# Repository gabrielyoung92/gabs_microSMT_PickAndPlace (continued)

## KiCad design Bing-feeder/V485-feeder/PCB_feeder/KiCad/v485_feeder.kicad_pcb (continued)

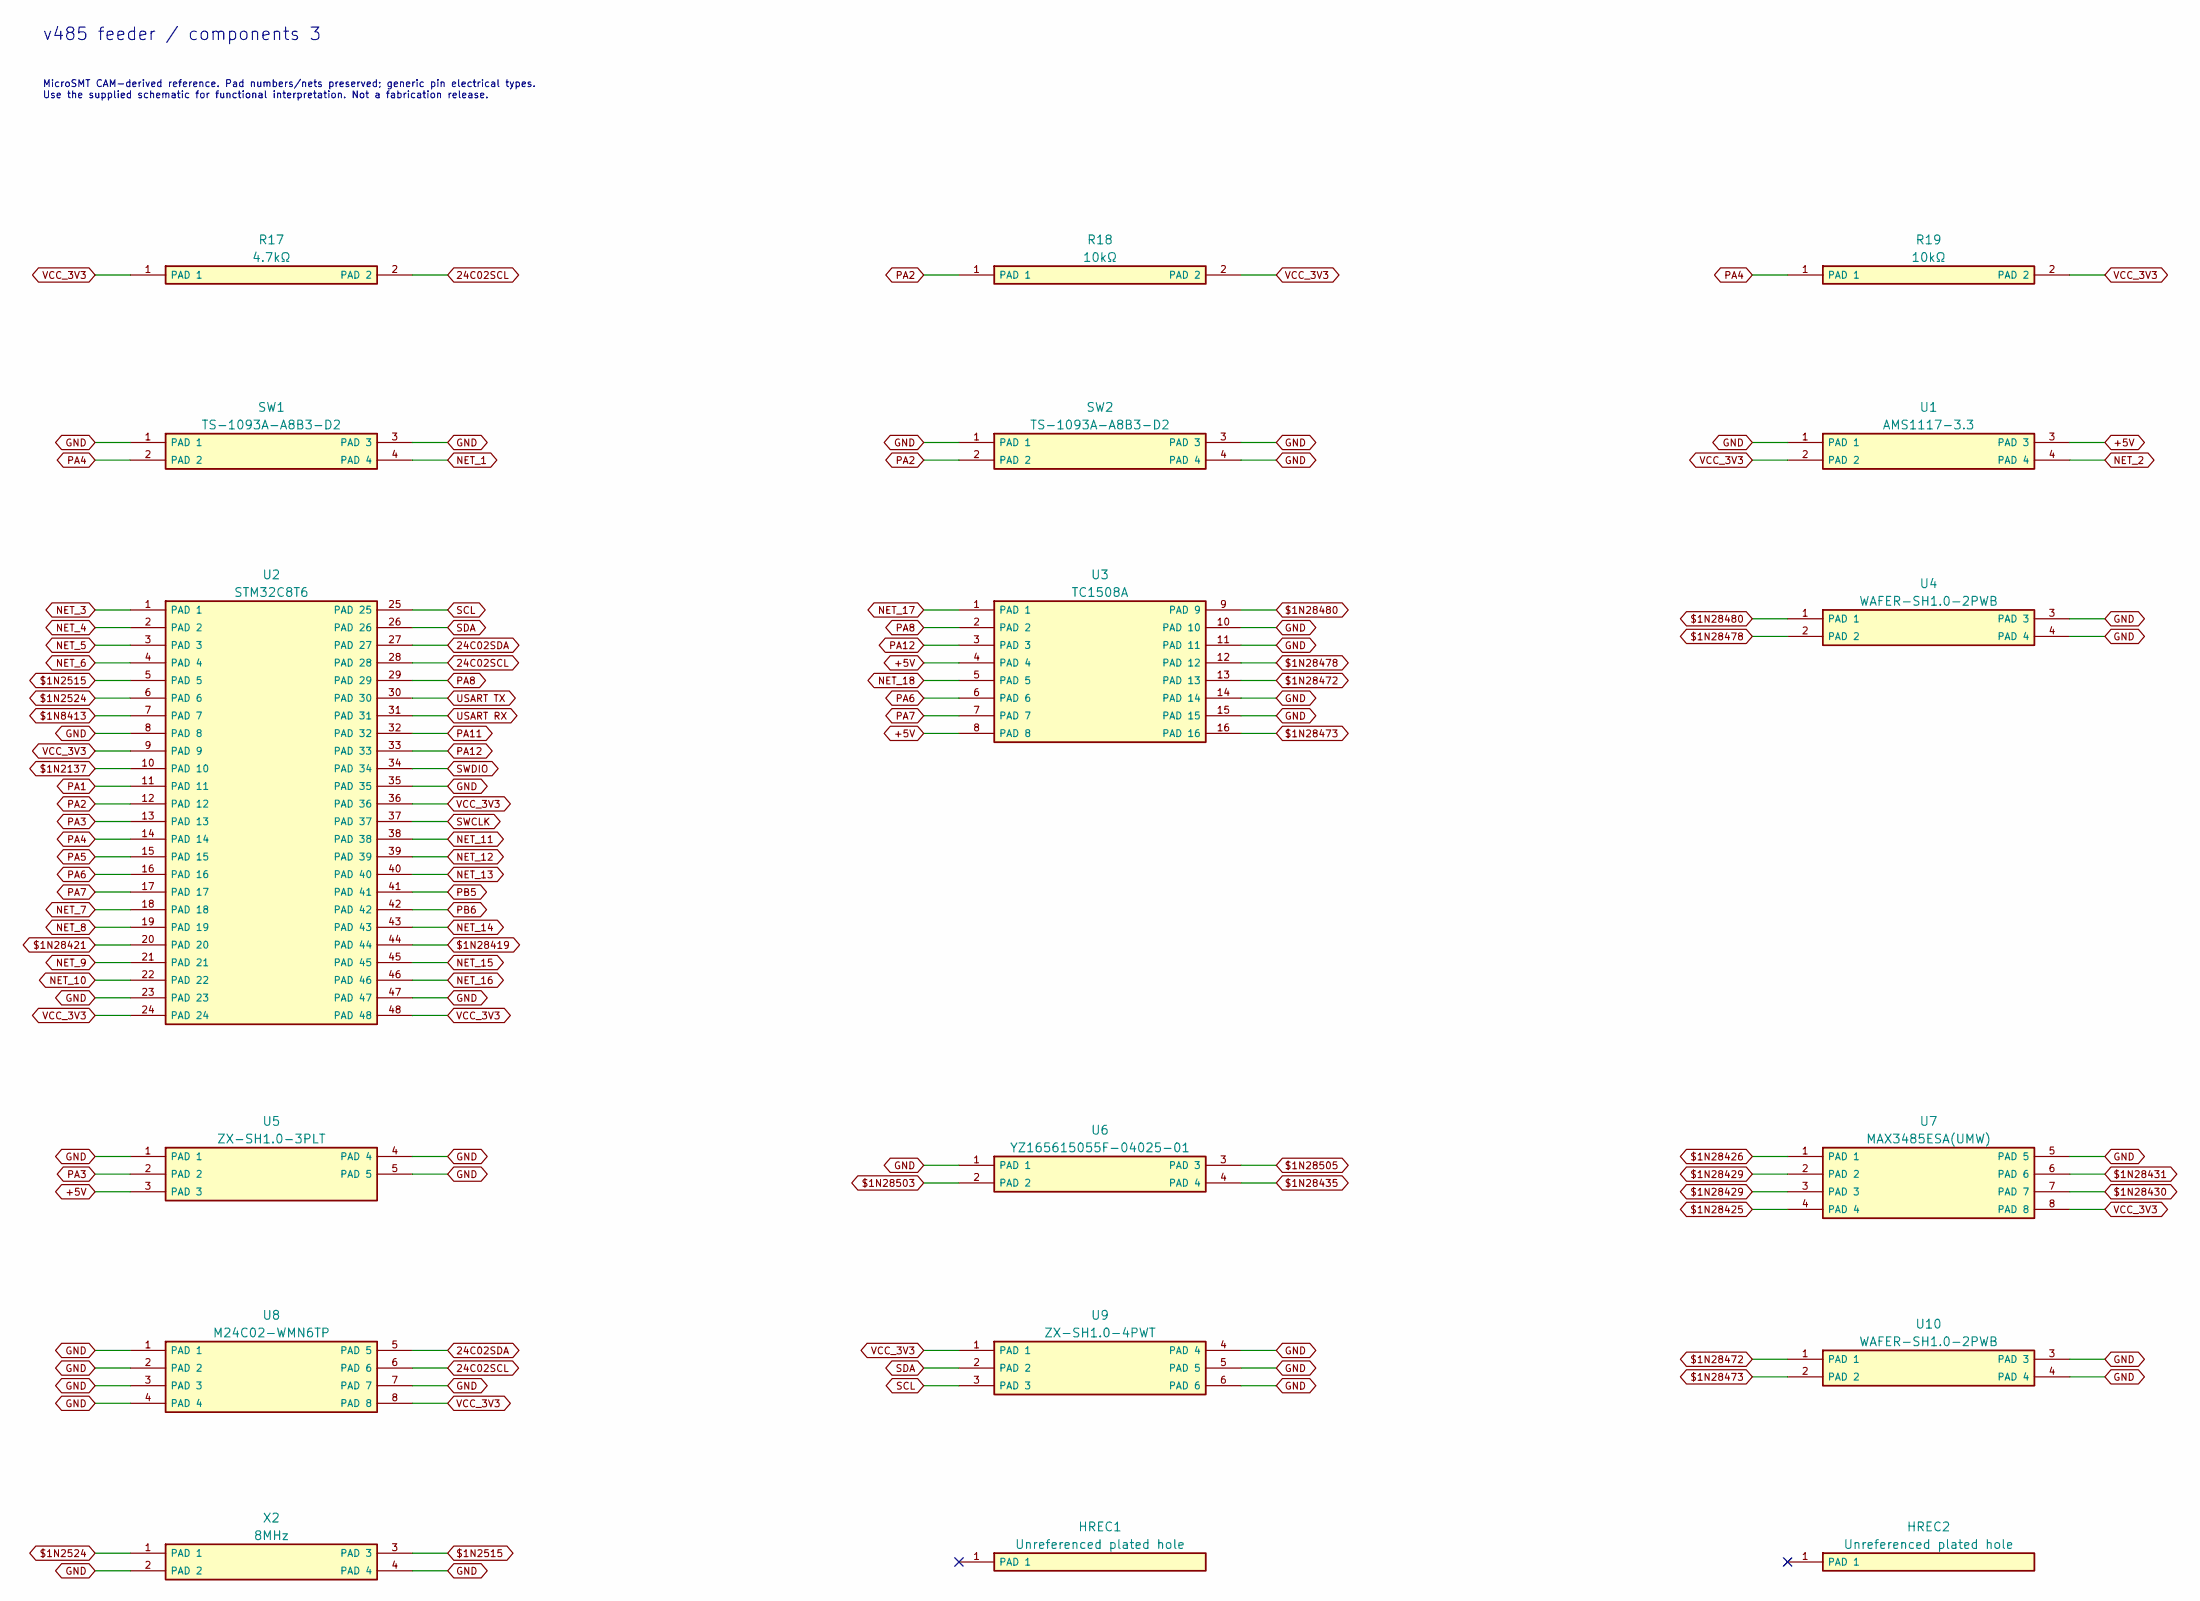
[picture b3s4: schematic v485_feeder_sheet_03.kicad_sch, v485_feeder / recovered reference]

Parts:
HREC1, HREC2: Unreferenced plated hole; PTH_1_c2bacda513
R17: 4.7kΩ; SMD_2_e7bda1677c
R18, R19: 10kΩ; SMD_2_e7bda1677c
SW1: TS-1093A-A8B3-D2; PTH_4_529d520394
SW2: TS-1093A-A8B3-D2; PTH_4_0f79a45cd4
U1: AMS1117-3.3; SMD_4_f5cc46188f
U2: STM32C8T6; SMD_48_b763d509fc
U3: TC1508A; SMD_16_ae7b02a39a
U4, U10: WAFER-SH1.0-2PWB; SMD_4_b0873716d4
U5: ZX-SH1.0-3PLT; SMD_5_2fbf7feada
U6: YZ165615055F-04025-01; SMD_4_36f36c5f38
U7: MAX3485ESA(UMW); SMD_8_e650e10851
U8: M24C02-WMN6TP; SMD_8_b02c488225
U9: ZX-SH1.0-4PWT; SMD_6_3f199f6944
X2: 8MHz; SMD_4_905bc3d9e5

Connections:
24C02SCL: R17.2 (PAD 2), U2.28 (PAD 28), U8.6 (PAD 6)
24C02SDA: U2.27 (PAD 27), U8.5 (PAD 5); also elsewhere on the board
$1N2137: U2.10 (PAD 10)
$1N2515: U2.5 (PAD 5), X2.3 (PAD 3); also elsewhere on the board
$1N2524: U2.6 (PAD 6), X2.1 (PAD 1); also elsewhere on the board
$1N8413: U2.7 (PAD 7); also elsewhere on the board
$1N28419: U2.44 (PAD 44); also elsewhere on the board
$1N28421: U2.20 (PAD 20); also elsewhere on the board
$1N28425: U7.4 (PAD 4); also elsewhere on the board
$1N28426: U7.1 (PAD 1); also elsewhere on the board
$1N28429: U7.2 (PAD 2), U7.3 (PAD 3); also elsewhere on the board
$1N28430: U7.7 (PAD 7); also elsewhere on the board
$1N28431: U7.6 (PAD 6); also elsewhere on the board
$1N28435: U6.4 (PAD 4); also elsewhere on the board
$1N28472: U3.13 (PAD 13), U10.1 (PAD 1); also elsewhere on the board
$1N28473: U3.16 (PAD 16), U10.2 (PAD 2); also elsewhere on the board
$1N28478: U3.12 (PAD 12), U4.2 (PAD 2); also elsewhere on the board
$1N28480: U3.9 (PAD 9), U4.1 (PAD 1); also elsewhere on the board
$1N28503: U6.2 (PAD 2); also elsewhere on the board
$1N28505: U6.3 (PAD 3); also elsewhere on the board
+5V: U1.3 (PAD 3), U3.4 (PAD 4), U3.8 (PAD 8), U5.3 (PAD 3); also elsewhere on the board
GND: SW1.1 (PAD 1), SW1.3 (PAD 3), SW2.1 (PAD 1), SW2.3 (PAD 3), SW2.4 (PAD 4), U1.1 (PAD 1), U2.8 (PAD 8), U2.23 (PAD 23), U2.35 (PAD 35), U2.47 (PAD 47), U3.10 (PAD 10), U3.11 (PAD 11), U3.14 (PAD 14), U3.15 (PAD 15), U4.3 (PAD 3), U4.4 (PAD 4), U5.1 (PAD 1), U5.4 (PAD 4), U5.5 (PAD 5), U6.1 (PAD 1), U7.5 (PAD 5), U8.1 (PAD 1), U8.2 (PAD 2), U8.3 (PAD 3), U8.4 (PAD 4), U8.7 (PAD 7), U9.4 (PAD 4), U9.5 (PAD 5), U9.6 (PAD 6), U10.3 (PAD 3), U10.4 (PAD 4), X2.2 (PAD 2), X2.4 (PAD 4); also elsewhere on the board
NET_1: SW1.4 (PAD 4)
NET_2: U1.4 (PAD 4)
NET_3: U2.1 (PAD 1)
NET_4: U2.2 (PAD 2)
NET_5: U2.3 (PAD 3)
NET_6: U2.4 (PAD 4)
NET_7: U2.18 (PAD 18)
NET_8: U2.19 (PAD 19)
NET_9: U2.21 (PAD 21)
NET_10: U2.22 (PAD 22)
NET_11: U2.38 (PAD 38)
NET_12: U2.39 (PAD 39)
NET_13: U2.40 (PAD 40)
NET_14: U2.43 (PAD 43)
NET_15: U2.45 (PAD 45)
NET_16: U2.46 (PAD 46)
NET_17: U3.1 (PAD 1)
NET_18: U3.5 (PAD 5)
PA1: U2.11 (PAD 11); also elsewhere on the board
PA2: R18.1 (PAD 1), SW2.2 (PAD 2), U2.12 (PAD 12); also elsewhere on the board
PA3: U2.13 (PAD 13), U5.2 (PAD 2); also elsewhere on the board
PA4: R19.1 (PAD 1), SW1.2 (PAD 2), U2.14 (PAD 14); also elsewhere on the board
PA5: U2.15 (PAD 15)
PA6: U2.16 (PAD 16), U3.6 (PAD 6)
PA7: U2.17 (PAD 17), U3.7 (PAD 7)
PA8: U2.29 (PAD 29), U3.2 (PAD 2)
PA11: U2.32 (PAD 32)
PA12: U2.33 (PAD 33), U3.3 (PAD 3)
PB5: U2.41 (PAD 41); also elsewhere on the board
PB6: U2.42 (PAD 42); also elsewhere on the board
SCL: U2.25 (PAD 25), U9.3 (PAD 3); also elsewhere on the board
SDA: U2.26 (PAD 26), U9.2 (PAD 2); also elsewhere on the board
SWCLK: U2.37 (PAD 37); also elsewhere on the board
SWDIO: U2.34 (PAD 34); also elsewhere on the board
USART RX: U2.31 (PAD 31); also elsewhere on the board
USART TX: U2.30 (PAD 30); also elsewhere on the board
VCC_3V3: R17.1 (PAD 1), R18.2 (PAD 2), R19.2 (PAD 2), U1.2 (PAD 2), U2.9 (PAD 9), U2.24 (PAD 24), U2.36 (PAD 36), U2.48 (PAD 48), U7.8 (PAD 8), U8.8 (PAD 8), U9.1 (PAD 1); also elsewhere on the board

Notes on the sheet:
v485 feeder / components 3
MicroSMT CAM-derived reference. Pad numbers/nets preserved; generic pin electrical types. Use the supplied schematic for functional interpretation. Not a fabrication release.

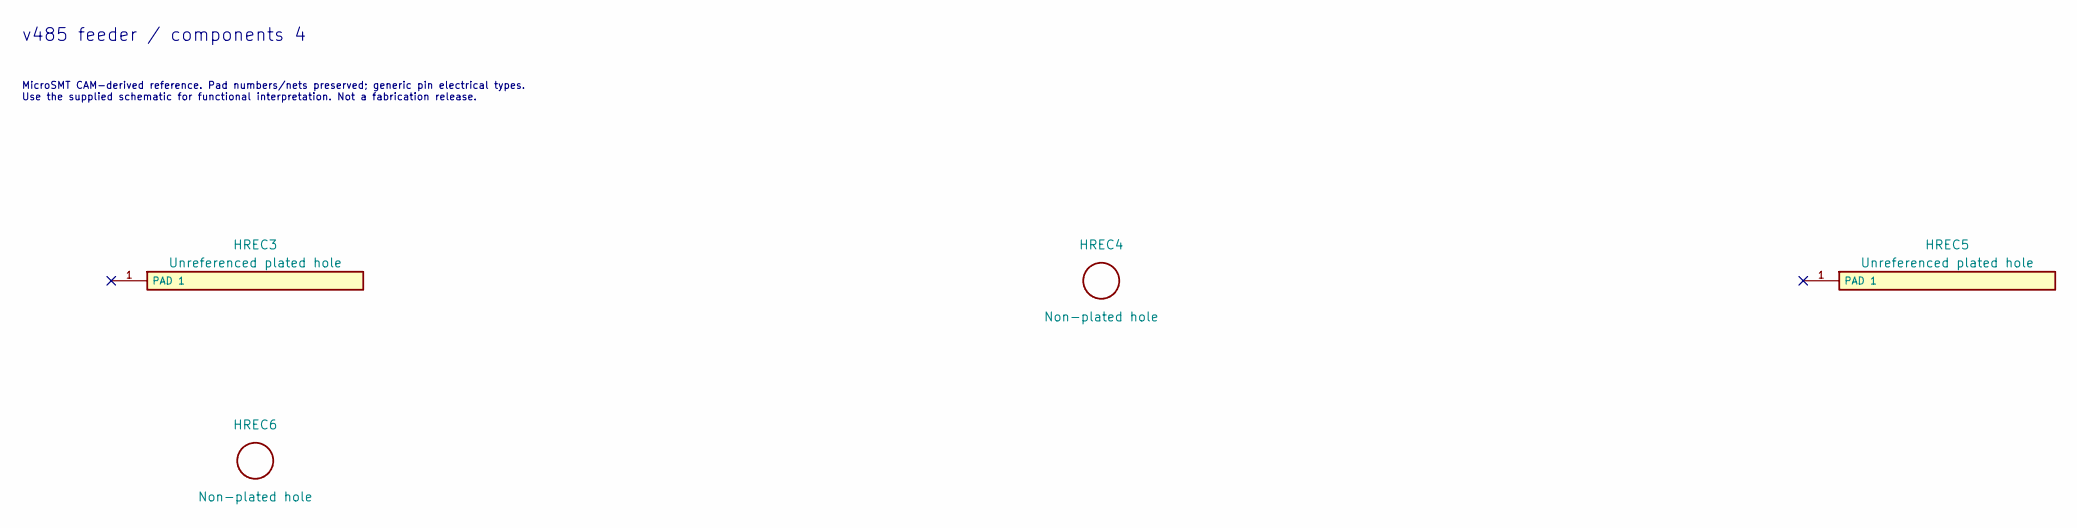
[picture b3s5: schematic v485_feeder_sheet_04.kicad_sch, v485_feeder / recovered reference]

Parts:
HREC3, HREC5: Unreferenced plated hole; PTH_1_c2bacda513
HREC4, HREC6: Non-plated hole; PTH_1_d65fec3626

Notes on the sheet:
v485 feeder / components 4
MicroSMT CAM-derived reference. Pad numbers/nets preserved; generic pin electrical types. Use the supplied schematic for functional interpretation. Not a fabrication release.

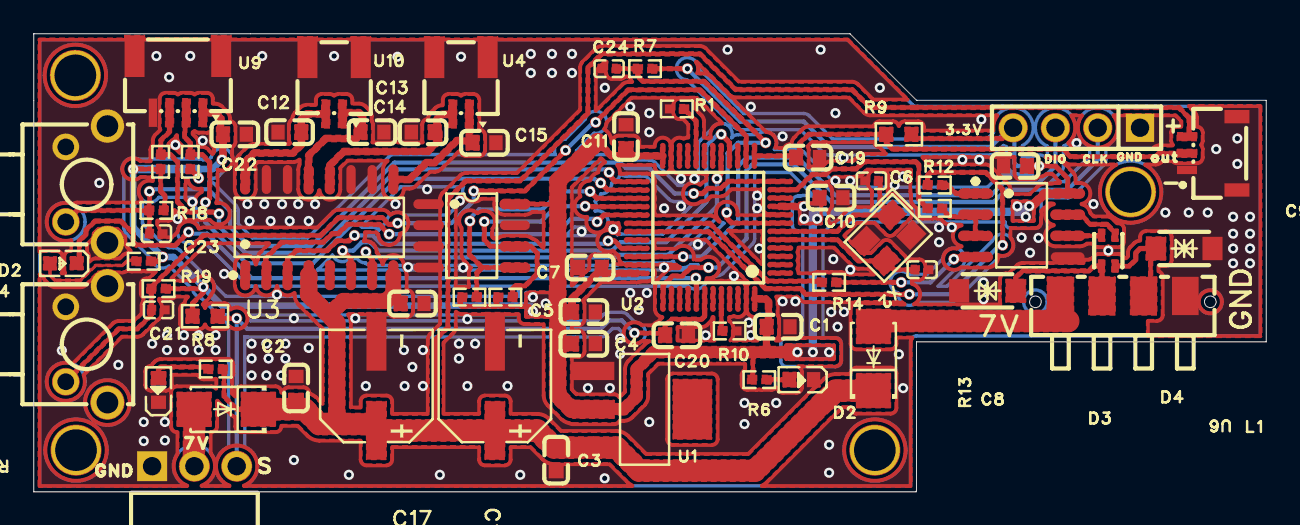
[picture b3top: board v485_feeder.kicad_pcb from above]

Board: 2 copper layers, 74.0 x 27.5 mm, 70 parts (0 on the bottom side), 42 nets.

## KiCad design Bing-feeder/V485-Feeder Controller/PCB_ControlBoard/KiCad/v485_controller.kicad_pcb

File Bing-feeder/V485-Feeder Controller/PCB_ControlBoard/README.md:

# V485 controller PCB

> Designs and original files by [MicroSMT](https://github.com/microsmt/Bing-feeder). [Credits and local changes](../../../CREDITS.md).

[Back to collection](../README.md)

Gerbers, editable KiCad files and previews are below.

## KiCad files

Open `.kicad_pro` in **KiCad 10**. Keep the whole `KiCad/` folder together; it contains the local libraries.

The schematics show pad numbers and connections. Use the supplied schematic for pin functions. Review the reported ERC/DRC findings before making a board.

| Project | Open in KiCad | Supporting reports |
| --- | --- | --- |
| V485 controller | [v485_controller.kicad_pro](KiCad/v485_controller.kicad_pro) | [Recovery](docs/recovery.json) · [Validation](docs/validation.json) |

[Recovery details](docs/KICAD_RECOVERY.md) · [Method and editing limits](../../../tools/kicad/RECOVERY_NOTES.md)

## Original board views

[Download Gerber ZIP](Gerber_PCB1_2026-10-09.zip)

<table>
<tr>
<td align="center"><br><sub>Top</sub></td>
<td align="center"><br><sub>Bottom</sub></td>
<td align="center"><br><sub>Top-side isometric</sub></td>
</tr>
</table>

## Schematics, parts lists and notes

- [BOM_Board1_Schematic1_2026-10-09.xlsx](docs/BOM_Board1_Schematic1_2026-10-09.xlsx)
- [SCH_Schematic1_2026-10-09.pdf](docs/SCH_Schematic1_2026-10-09.pdf)

Gerber previews use display colours and an assumed 1.6 mm thickness; use source data for manufacturing dimensions.

## KiCad previews

KiCad reconstruction views; source Gerber views are above.

### V485 controller

<table>
<tr>
<td align="center"><br><sub>Recovered schematic</sub></td>
<td align="center"><br><sub>Recovered PCB top</sub></td>
<td align="center"><br><sub>Recovered PCB bottom</sub></td>
</tr>
</table>

[Sheet overview](photos/kicad-v485_controller-overview.jpg) · [Components 1](photos/kicad-v485_controller-sheet-01.jpg) · [Components 2](photos/kicad-v485_controller-sheet-02.jpg)

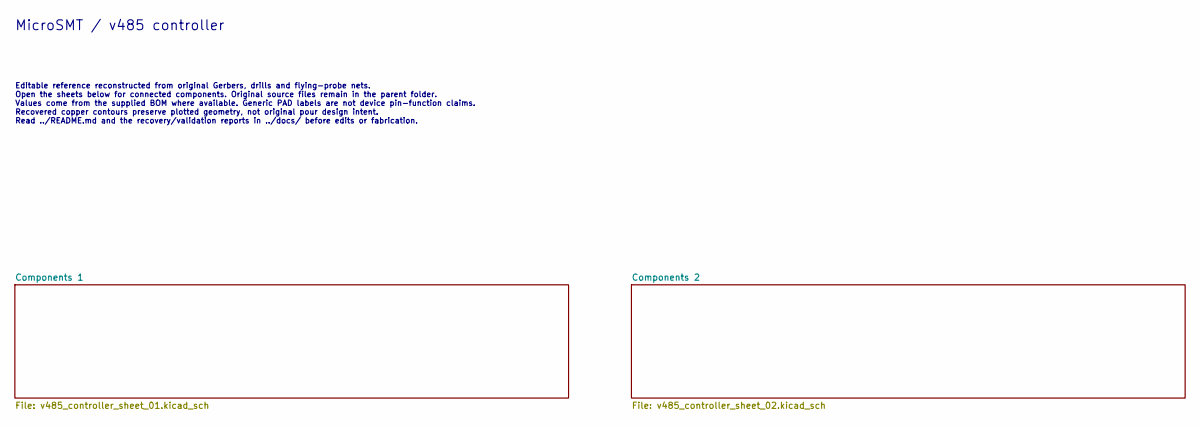
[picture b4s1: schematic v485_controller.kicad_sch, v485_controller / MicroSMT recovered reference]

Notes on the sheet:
MicroSMT / v485 controller
Editable reference reconstructed from original Gerbers, drills and flying-probe nets. Open the sheets below for connected components. Original source files remain in the parent folder. Values come from the supplied BOM where available. Generic PAD labels are not device pin-function claims. Recovere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

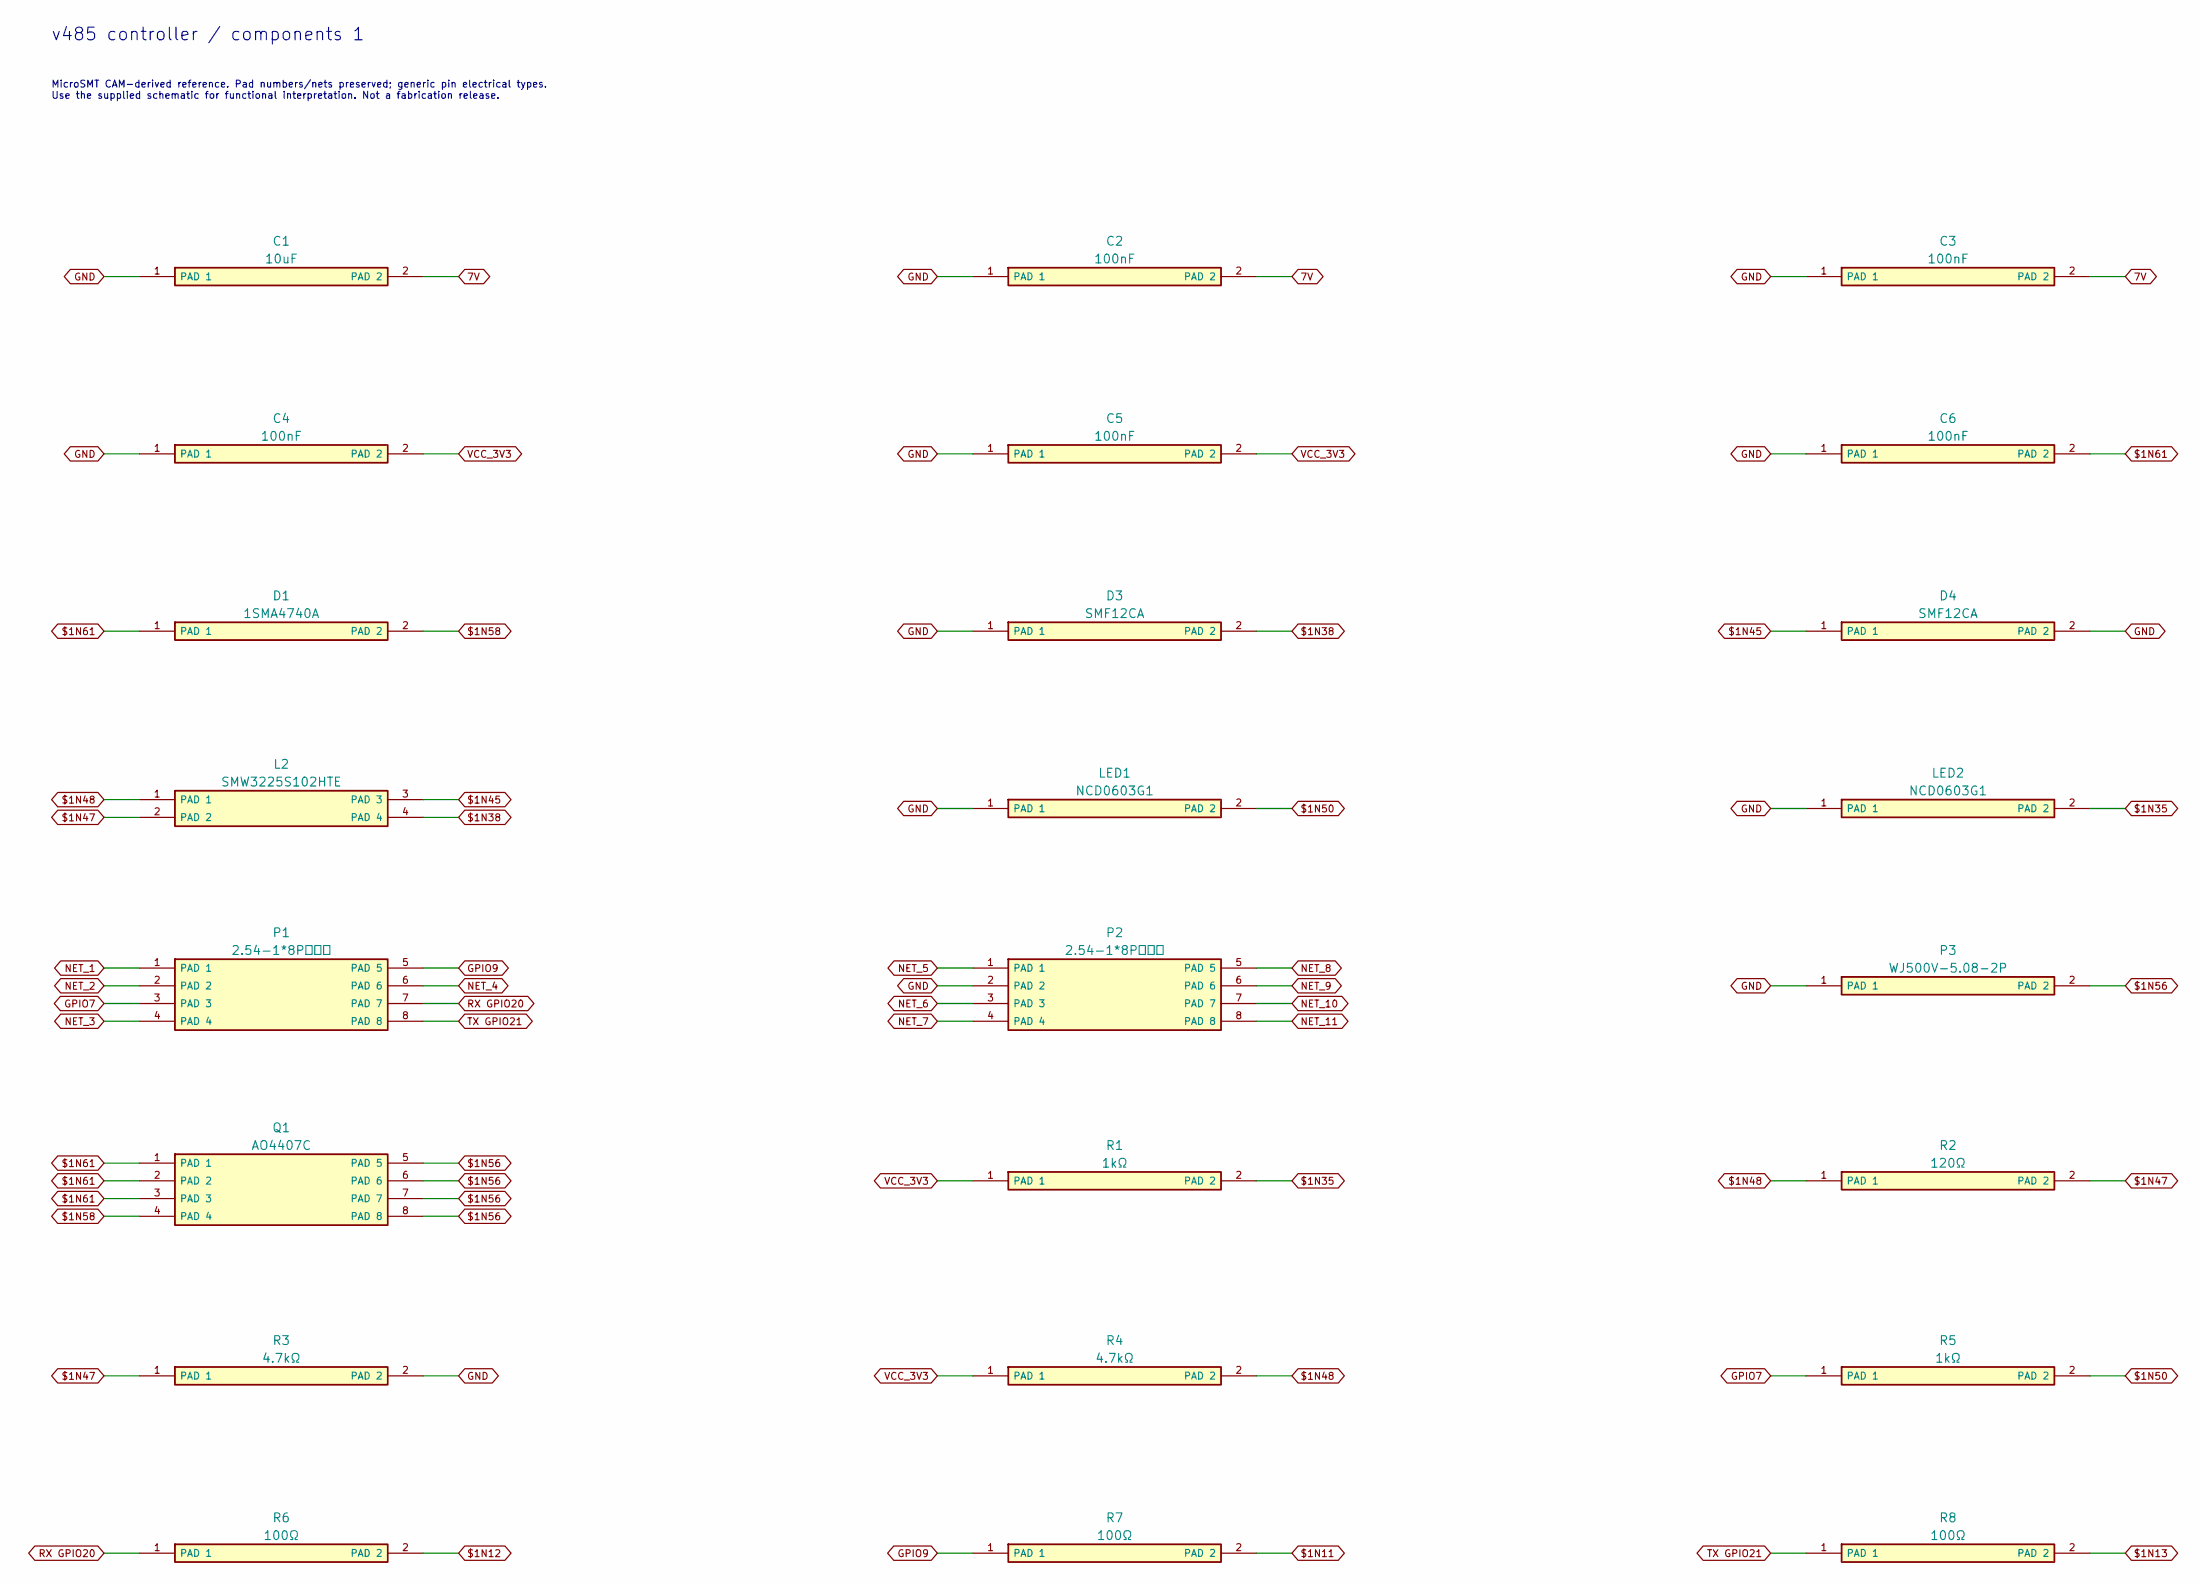
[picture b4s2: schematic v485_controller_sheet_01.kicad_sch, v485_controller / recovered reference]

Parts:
C1: 10uF; SMD_2_7371bf4a95
C2, C6: 100nF; SMD_2_723c4baacf
C3, C4: 100nF; SMD_2_7371bf4a95
C5: 100nF; SMD_2_c1a3413776
D1: 1SMA4740A; SMD_2_1fa9734501
D3, D4: SMF12CA; SMD_2_55f911f37a
L2: SMW3225S102HTE; SMD_4_008e72132e
LED1: NCD0603G1; SMD_2_aee0334fb4
LED2: NCD0603G1; SMD_2_7119c32529
P1: 2.54-1*8P母环保; PTH_8_ac2e14a8f3
P2: 2.54-1*8P母环保; PTH_8_7aeb1c419b
P3: WJ500V-5.08-2P; PTH_2_e96cc44099
Q1: AO4407C; SMD_8_0b8baf6ad0
R1: 1kΩ; SMD_2_cc916b3528
R2: 120Ω; SMD_2_a7994fb989
R3, R4: 4.7kΩ; SMD_2_a7994fb989
R5: 1kΩ; SMD_2_04577a26f8
R6: 100Ω; SMD_2_cc916b3528
R7, R8: 100Ω; SMD_2_fef7677169

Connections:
7V: C1.2 (PAD 2), C2.2 (PAD 2), C3.2 (PAD 2); also elsewhere on the board
$1N11: R7.2 (PAD 2); also elsewhere on the board
$1N12: R6.2 (PAD 2); also elsewhere on the board
$1N13: R8.2 (PAD 2); also elsewhere on the board
$1N35: LED2.2 (PAD 2), R1.2 (PAD 2)
$1N38: D3.2 (PAD 2), L2.4 (PAD 4); also elsewhere on the board
$1N45: D4.1 (PAD 1), L2.3 (PAD 3); also elsewhere on the board
$1N47: L2.2 (PAD 2), R2.2 (PAD 2), R3.1 (PAD 1); also elsewhere on the board
$1N48: L2.1 (PAD 1), R2.1 (PAD 1), R4.2 (PAD 2); also elsewhere on the board
$1N50: LED1.2 (PAD 2), R5.2 (PAD 2)
$1N56: P3.2 (PAD 2), Q1.5 (PAD 5), Q1.6 (PAD 6), Q1.7 (PAD 7), Q1.8 (PAD 8)
$1N58: D1.2 (PAD 2), Q1.4 (PAD 4); also elsewhere on the board
$1N61: C6.2 (PAD 2), D1.1 (PAD 1), Q1.1 (PAD 1), Q1.2 (PAD 2), Q1.3 (PAD 3); also elsewhere on the board
GND: C1.1 (PAD 1), C2.1 (PAD 1), C3.1 (PAD 1), C4.1 (PAD 1), C5.1 (PAD 1), C6.1 (PAD 1), D3.1 (PAD 1), D4.2 (PAD 2), LED1.1 (PAD 1), LED2.1 (PAD 1), P2.2 (PAD 2), P3.1 (PAD 1), R3.2 (PAD 2); also elsewhere on the board
GPIO7: P1.3 (PAD 3), R5.1 (PAD 1)
GPIO9: P1.5 (PAD 5), R7.1 (PAD 1)
NET_1: P1.1 (PAD 1)
NET_2: P1.2 (PAD 2)
NET_3: P1.4 (PAD 4)
NET_4: P1.6 (PAD 6)
NET_5: P2.1 (PAD 1)
NET_6: P2.3 (PAD 3)
NET_7: P2.4 (PAD 4)
NET_8: P2.5 (PAD 5)
NET_9: P2.6 (PAD 6)
NET_10: P2.7 (PAD 7)
NET_11: P2.8 (PAD 8)
RX GPIO20: P1.7 (PAD 7), R6.1 (PAD 1)
TX GPIO21: P1.8 (PAD 8), R8.1 (PAD 1)
VCC_3V3: C4.2 (PAD 2), C5.2 (PAD 2), R1.1 (PAD 1), R4.1 (PAD 1); also elsewhere on the board

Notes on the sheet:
v485 controller / components 1
MicroSMT CAM-derived reference. Pad numbers/nets preserved; generic pin electrical types. Use the supplied schematic for functional interpretation. Not a fabrication release.

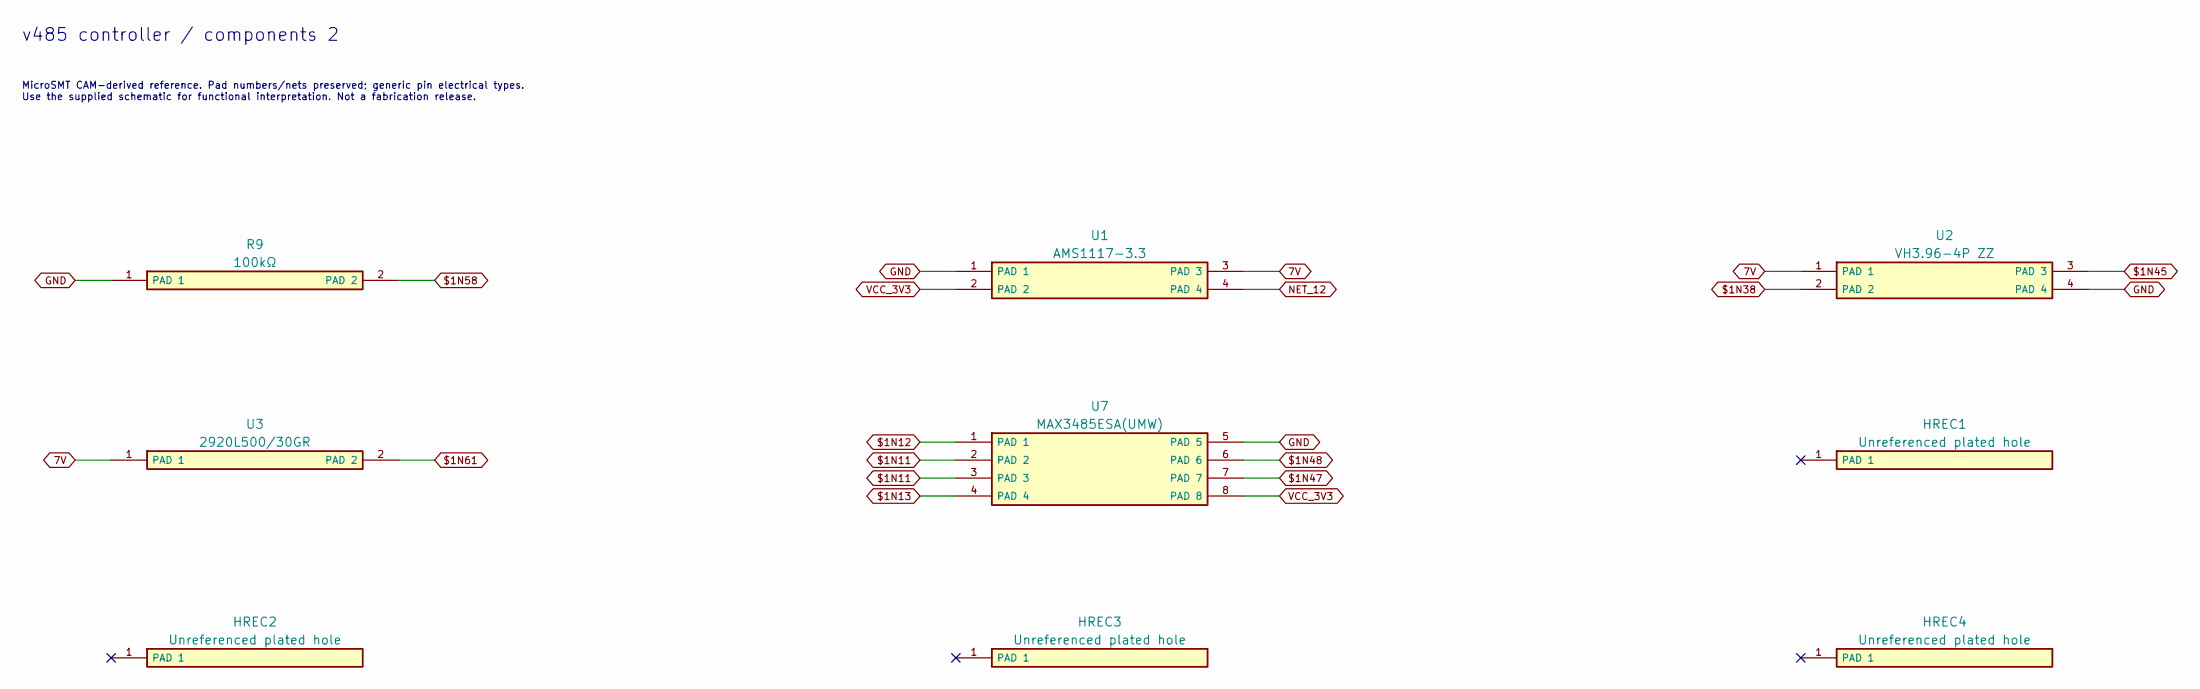
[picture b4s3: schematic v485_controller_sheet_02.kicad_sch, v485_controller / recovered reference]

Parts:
HREC1, HREC2, HREC3, HREC4: Unreferenced plated hole; PTH_1_ee2b9368a9
R9: 100kΩ; SMD_2_cc916b3528
U1: AMS1117-3.3; SMD_4_f5cc46188f
U2: VH3.96-4P ZZ; PTH_4_101e17f868
U3: 2920L500/30GR; SMD_2_74179e062f
U7: MAX3485ESA(UMW); SMD_8_f52f094fb5

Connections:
7V: U1.3 (PAD 3), U2.1 (PAD 1), U3.1 (PAD 1); also elsewhere on the board
$1N11: U7.2 (PAD 2), U7.3 (PAD 3); also elsewhere on the board
$1N12: U7.1 (PAD 1); also elsewhere on the board
$1N13: U7.4 (PAD 4); also elsewhere on the board
$1N38: U2.2 (PAD 2); also elsewhere on the board
$1N45: U2.3 (PAD 3); also elsewhere on the board
$1N47: U7.7 (PAD 7); also elsewhere on the board
$1N48: U7.6 (PAD 6); also elsewhere on the board
$1N58: R9.2 (PAD 2); also elsewhere on the board
$1N61: U3.2 (PAD 2); also elsewhere on the board
GND: R9.1 (PAD 1), U1.1 (PAD 1), U2.4 (PAD 4), U7.5 (PAD 5); also elsewhere on the board
NET_12: U1.4 (PAD 4)
VCC_3V3: U1.2 (PAD 2), U7.8 (PAD 8); also elsewhere on the board

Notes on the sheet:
v485 controller / components 2
MicroSMT CAM-derived reference. Pad numbers/nets preserved; generic pin electrical types. Use the supplied schematic for functional interpretation. Not a fabrication release.

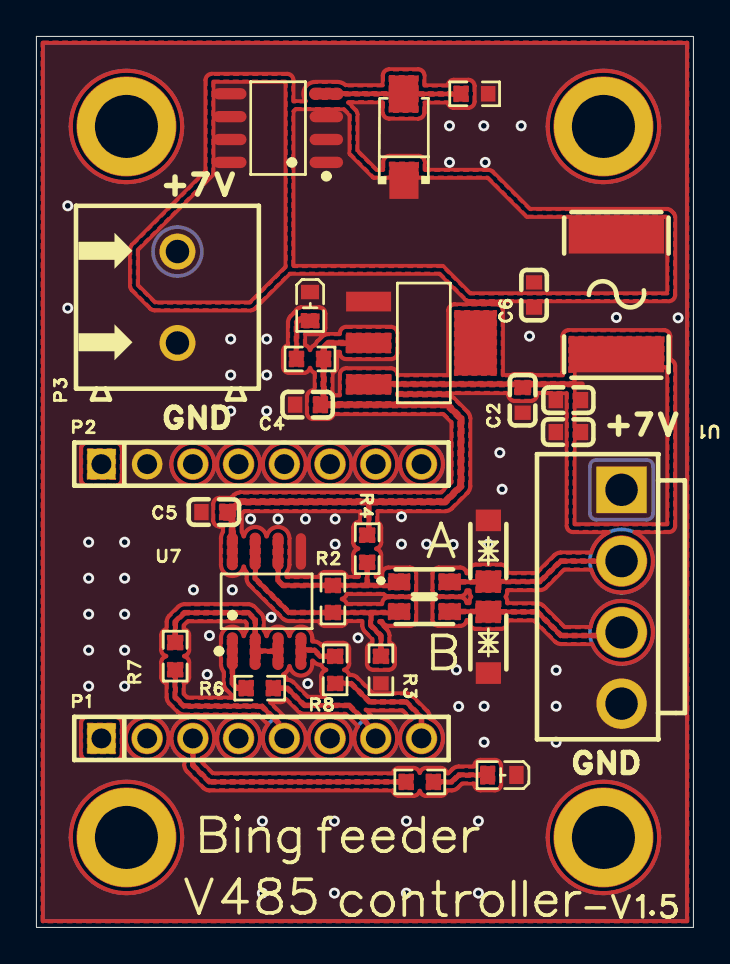
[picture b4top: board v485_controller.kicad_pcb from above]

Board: 2 copper layers, 36.5 x 49.5 mm, 33 parts (0 on the bottom side), 19 nets.

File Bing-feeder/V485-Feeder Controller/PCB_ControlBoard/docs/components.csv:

Reference,Value,Recovered footprint,Pad count,Inferred reference
C1,10uF,MicroSMT_v485_controller:SMD_2_7371bf4a95,2,False
C2,100nF,MicroSMT_v485_controller:SMD_2_723c4baacf,2,False
C3,100nF,MicroSMT_v485_controller:SMD_2_7371bf4a95,2,False
C4,100nF,MicroSMT_v485_controller:SMD_2_7371bf4a95,2,False
C5,100nF,MicroSMT_v485_controller:SMD_2_c1a3413776,2,False
C6,100nF,MicroSMT_v485_controller:SMD_2_723c4baacf,2,False
D1,1SMA4740A,MicroSMT_v485_controller:SMD_2_1fa9734501,2,False
D3,SMF12CA,MicroSMT_v485_controller:SMD_2_55f911f37a,2,False
D4,SMF12CA,MicroSMT_v485_controller:SMD_2_55f911f37a,2,False
L2,SMW3225S102HTE,MicroSMT_v485_controller:SMD_4_008e72132e,4,False
LED1,NCD0603G1,MicroSMT_v485_controller:SMD_2_aee0334fb4,2,False
LED2,NCD0603G1,MicroSMT_v485_controller:SMD_2_7119c32529,2,False
P1,2.54-1*8P母环保,MicroSMT_v485_controller:PTH_8_ac2e14a8f3,8,False
P2,2.54-1*8P母环保,MicroSMT_v485_controller:PTH_8_7aeb1c419b,8,False
P3,WJ500V-5.08-2P,MicroSMT_v485_controller:PTH_2_e96cc44099,2,False
Q1,AO4407C,MicroSMT_v485_controller:SMD_8_0b8baf6ad0,8,False
R1,1kΩ,MicroSMT_v485_controller:SMD_2_cc916b3528,2,False
R2,120Ω,MicroSMT_v485_controller:SMD_2_a7994fb989,2,False
R3,4.7kΩ,MicroSMT_v485_controller:SMD_2_a7994fb989,2,False
R4,4.7kΩ,MicroSMT_v485_controller:SMD_2_a7994fb989,2,False
R5,1kΩ,MicroSMT_v485_controller:SMD_2_04577a26f8,2,False
R6,100Ω,MicroSMT_v485_controller:SMD_2_cc916b3528,2,False
R7,100Ω,MicroSMT_v485_controller:SMD_2_fef7677169,2,False
R8,100Ω,MicroSMT_v485_controller:SMD_2_fef7677169,2,False
R9,100kΩ,MicroSMT_v485_controller:SMD_2_cc916b3528,2,False
U1,AMS1117-3.3,MicroSMT_v485_controller:SMD_4_f5cc46188f,4,False
U2,VH3.96-4P ZZ,MicroSMT_v485_controller:PTH_4_101e17f868,4,False
U3,2920L500/30GR,MicroSMT_v485_controller:SMD_2_74179e062f,2,False
U7,MAX3485ESA(UMW),MicroSMT_v485_controller:SMD_8_f52f094fb5,8,False
HREC1,Unreferenced plated hole,MicroSMT_v485_controller:PTH_1_ee2b9368a9,1,True
HREC2,Unreferenced plated hole,MicroSMT_v485_controller:PTH_1_ee2b9368a9,1,True
HREC3,Unreferenced plated hole,MicroSMT_v485_controller:PTH_1_ee2b9368a9,1,True
HREC4,Unreferenced plated hole,MicroSMT_v485_controller:PTH_1_ee2b9368a9,1,True

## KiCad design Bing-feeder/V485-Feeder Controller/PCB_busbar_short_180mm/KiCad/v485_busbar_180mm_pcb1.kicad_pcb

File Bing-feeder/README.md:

# Bing feeders and controllers

> Designs and original files by [MicroSMT](https://github.com/microsmt/Bing-feeder). [Credits and local changes](../CREDITS.md).

Choose V3 or V485 below. Each has its own models, board files, firmware and assembly notes.

| Browse | Contents |
| --- | --- |
| [Powered-feeder dashboard](V485-feeder/USB_host/README.md) | PC host, firmware updates, configuration, stock and OpenPnP integration |
| [V485 feeder](V485-feeder/README.md) | 8/12/16/24 mm mechanics, shared parts, feeder/display PCBs and STM32 sources |
| [V485 controller](V485-Feeder%20Controller/README.md) | ESP32-C3 PlatformIO firmware, controller PCB and RS485 busbars |
| [V3 feeder](V3-feeder/README.md) | 8/12/16/24 mm parts, shared parts, STM32 sources and manuals |
| [V3 controller](V3-Feeder%20Controller/README.md) | Mega2560 sketch, controller board and feeder busbars |
| [STM32 build guide](STM32-BUILD.txt) | Universal V485 PlatformIO build and V3 source requirements |
| [License](LICENSE) | Supplied upstream license |

Vendor files checked on 30 October 2026: no file changes.
[Source comparison](UPSTREAM-2026-10-25.md).

## Vendor reference photo

Original MicroSMT photo from `Doc/微信图片_20250123114300.jpg`.

## About Bing feeders

MicroSMT’s Bing feeder uses a sprocket and position sensor to advance component tape. It was designed for the PNPv3 and can be triggered by a high-level pulse through OpenPnP’s ReferenceAutoFeeder. Using it on another machine still needs the right wiring and control setup.

Kits: [microsmt.com.cn](https://www.microsmt.com.cn) · Support: [Discord](https://discord.gg/qT7ZAAgspy) · [Google group](https://groups.google.com/g/pnpv3-bing-feeder)

### Position sensing
An optical sensor tracks the sprocket position so the feeder can control how far the tape advances.

### Tape support
The elastic pad underneath accommodates different tape thicknesses and helps reduce vibration and parts bouncing out.

### Magnetic mounting
The magnetic mount lets you remove and swap feeders quickly.

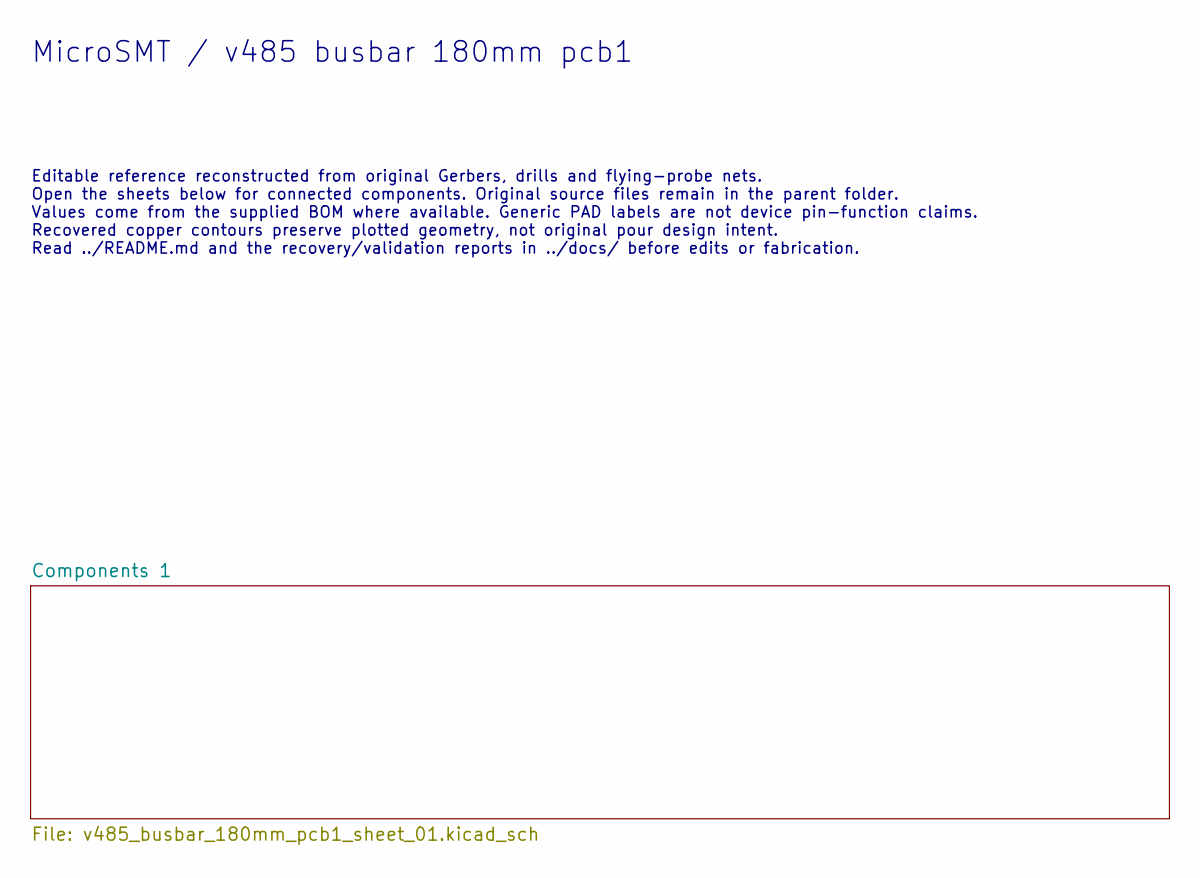
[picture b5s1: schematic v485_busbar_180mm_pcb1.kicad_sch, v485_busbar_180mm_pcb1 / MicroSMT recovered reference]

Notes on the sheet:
MicroSMT / v485 busbar 180mm pcb1
Editable reference reconstructed from original Gerbers, drills and flying-probe nets. Open the sheets below for connected components. Original source files remain in the parent folder. Values come from the supplied BOM where available. Generic PAD labels are not device pin-function claims. Recovere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

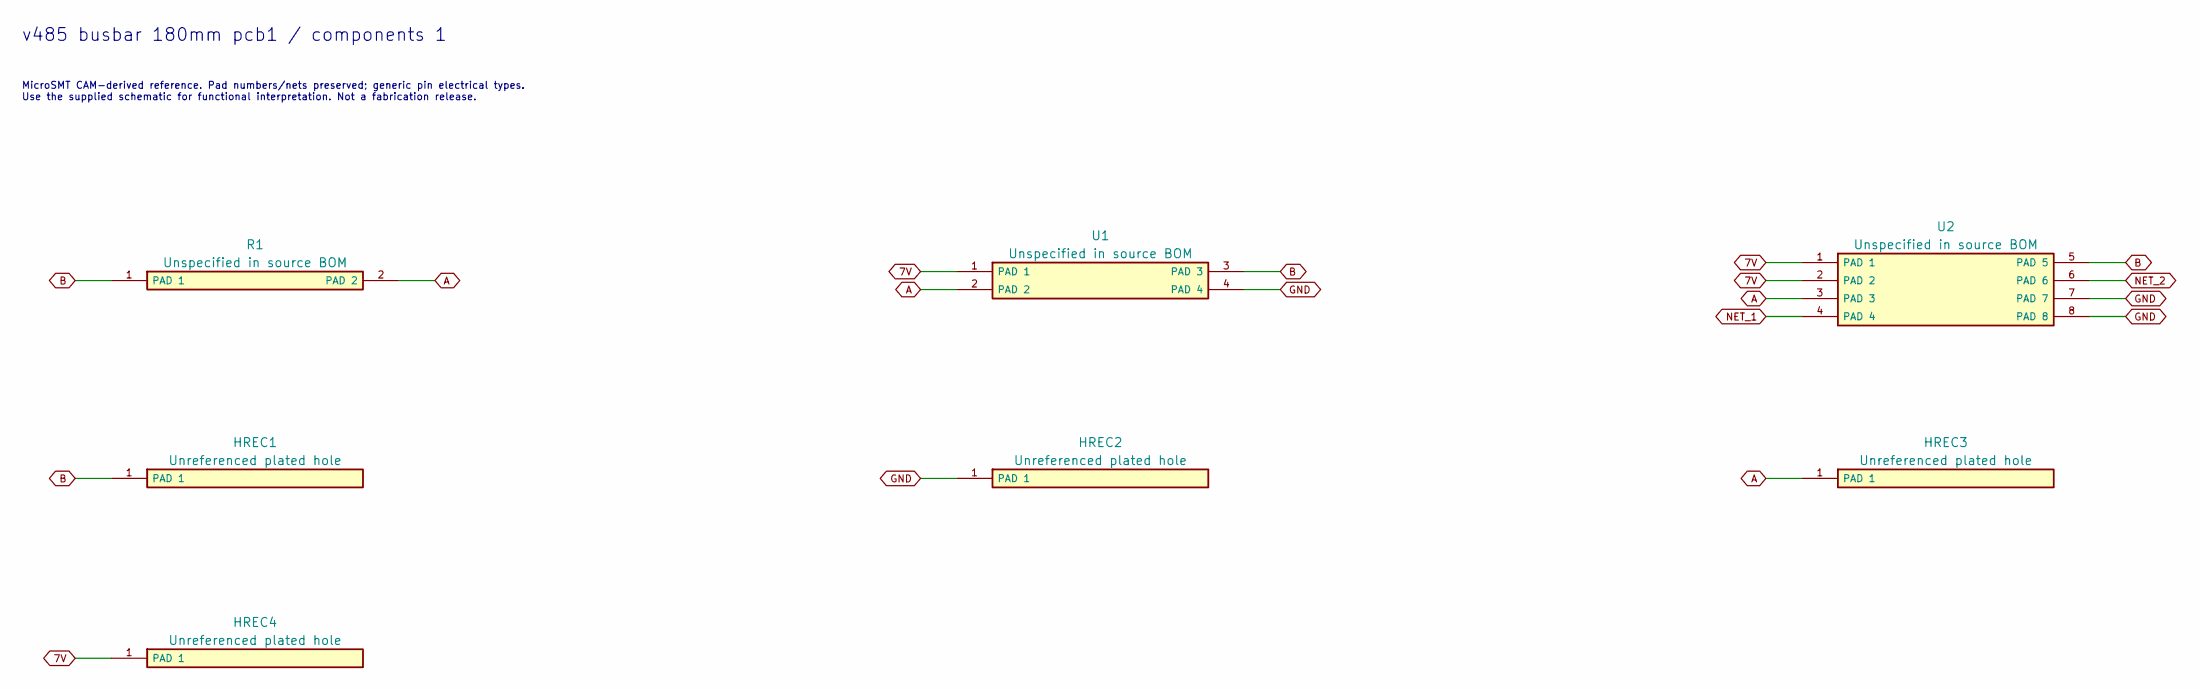
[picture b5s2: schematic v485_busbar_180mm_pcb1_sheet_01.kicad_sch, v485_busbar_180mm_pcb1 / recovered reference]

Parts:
HREC1, HREC2, HREC3, HREC4: Unreferenced plated hole; PTH_1_d32e30a0ea
R1: Unspecified in source BOM; SMD_2_fef7677169
U1: Unspecified in source BOM; PTH_4_06e8961db4
U2: Unspecified in source BOM; SMD_8_a8244cd5c0

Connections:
7V: HREC4.1, U1.1 (PAD 1), U2.1 (PAD 1), U2.2 (PAD 2)
A: HREC3.1, R1.2 (PAD 2), U1.2 (PAD 2), U2.3 (PAD 3)
B: HREC1.1, R1.1 (PAD 1), U1.3 (PAD 3), U2.5 (PAD 5)
GND: HREC2.1, U1.4 (PAD 4), U2.7 (PAD 7), U2.8 (PAD 8)
NET_1: U2.4 (PAD 4)
NET_2: U2.6 (PAD 6)

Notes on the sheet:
v485 busbar 180mm pcb1 / components 1
MicroSMT CAM-derived reference. Pad numbers/nets preserved; generic pin electrical types. Use the supplied schematic for functional interpretation. Not a fabrication release.

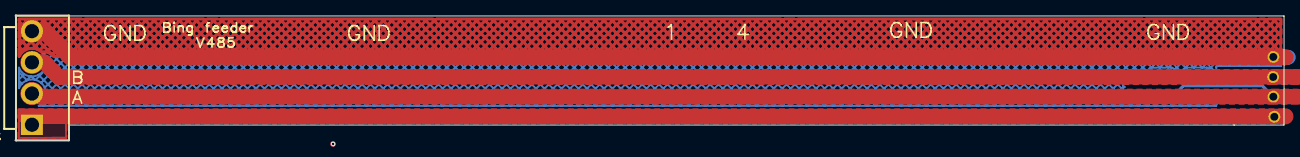
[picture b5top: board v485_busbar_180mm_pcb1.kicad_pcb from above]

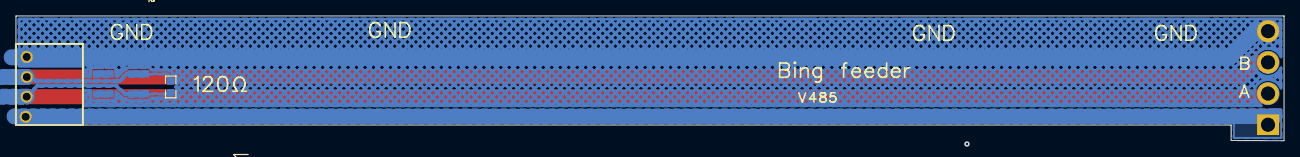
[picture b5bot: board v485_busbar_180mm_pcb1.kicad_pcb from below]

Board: 2 copper layers, 161.0 x 15.8 mm, 7 parts (2 on the bottom side), 4 nets.
